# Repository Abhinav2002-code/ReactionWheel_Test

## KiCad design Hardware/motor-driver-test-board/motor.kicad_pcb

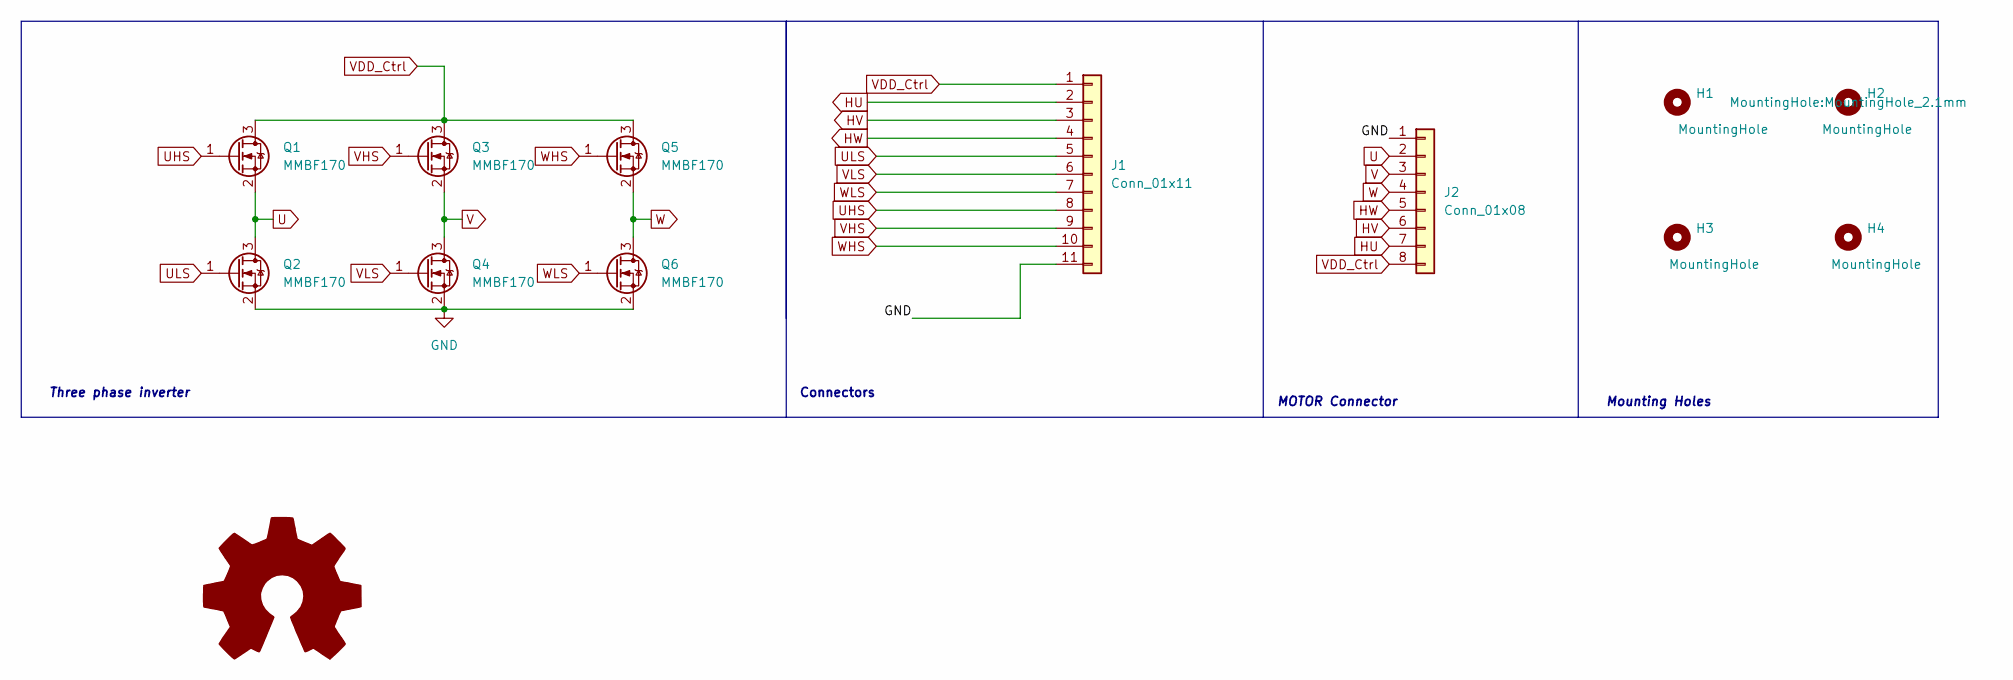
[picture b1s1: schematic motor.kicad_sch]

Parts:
H1, H2, H3, H4: MountingHole; MountingHole_2.1mm
J1: Conn_01x11; PinHeader_1x11_P2.54mm_Horizontal
J2: Conn_01x08; PinHeader_1x08_P1.00mm_Horizontal
Q1, Q2, Q3, Q4, Q5, Q6: MMBF170; SOT-23

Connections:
GND: J1.11, J2.1, Q2.2 (S), Q4.2 (S), Q6.2 (S)
HU: J1.2, J2.7
HV: J1.3, J2.6
HW: J1.4, J2.5
U: J2.2, Q1.2 (S), Q2.3 (D)
UHS: J1.8, Q1.1 (G)
ULS: J1.5, Q2.1 (G)
V: J2.3, Q3.2 (S), Q4.3 (D)
VDD_Ctrl: J1.1, J2.8, Q1.3 (D), Q3.3 (D), Q5.3 (D)
VHS: J1.9, Q3.1 (G)
VLS: J1.6, Q4.1 (G)
W: J2.4, Q5.2 (S), Q6.3 (D)
WHS: J1.10, Q5.1 (G)
WLS: J1.7, Q6.1 (G)

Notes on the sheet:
Three phase inverter
MOTOR Connector
Mounting Holes
Connectors

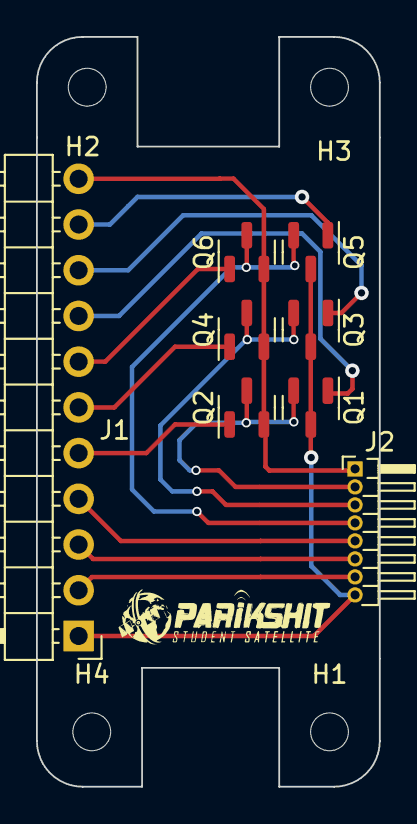
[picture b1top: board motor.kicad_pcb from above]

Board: 2 copper layers, 19.0 x 41.7 mm, 12 parts (0 on the bottom side), 14 nets.

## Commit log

2022-08-28 Files arranged properly
2022-08-28 net labels changed to U V W
2022-08-28 layout initialised and redundant u v w signals taken away from J1
2022-08-28 PCB REV 1.0
2022-08-28 All connections completed on board & GND border added for testing convenience
2022-09-06 power polygons changed to trace, connector position shifted to the edge and boundary changed
